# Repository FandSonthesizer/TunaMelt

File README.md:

# TunaMelt
Our Tuna Melt clone. 

This is out attempt to build a Tuna Melt clone. We changed it to have a true bypass, also we are using standart parts which are not hard to get by.
The Vactrol consists of an LDR03 light sensitive resistor and a white 3mm LED, bound together head on head with some black electrical tape.

So we re-named it the FnS Melt. :-)

This effect just sounds great, a very nice Tremolo indeed!

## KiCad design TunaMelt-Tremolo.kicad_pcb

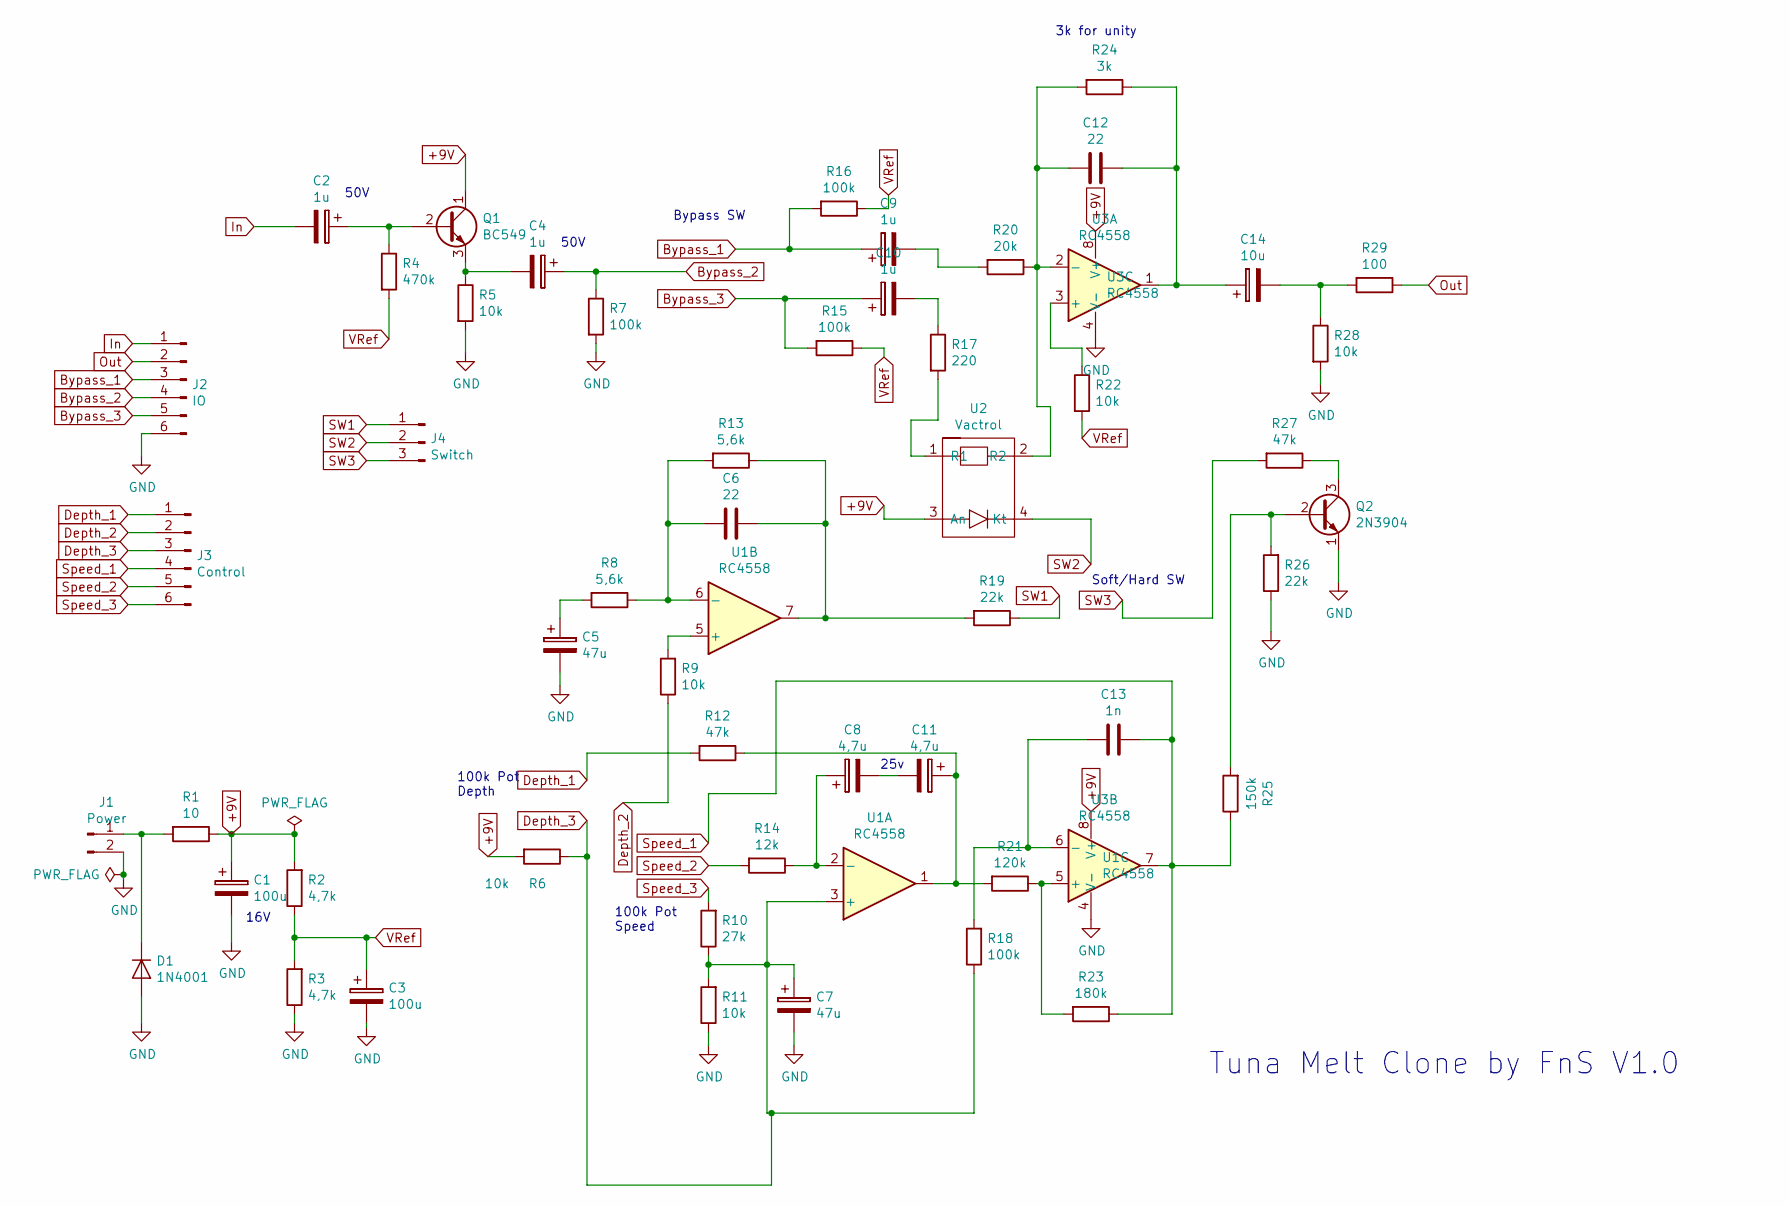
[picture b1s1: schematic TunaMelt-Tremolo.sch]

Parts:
C1, C3: 100u; Elko_D6.3mm_P2.50mm
C2, C4, C9, C10: 1u; Elko_D6.3mm_P2.50mm
C5, C7: 47u; Elko_D6.3mm_P2.50mm
C6, C12: 22; Kondensator_Keramik
C8, C11: 4,7u; Elko_D6.3mm_P2.50mm
C13: 1n; Kondensator_Keramik
C14: 10u; Elko_D6.3mm_P2.50mm
D1: 1N4001; Diode_Horizontal
J1: Power; Stift_x02
J2: IO; PinHeader_1x06_P2.54mm_Vertical_NIK
J3: Control; PinHeader_1x06_P2.54mm_Vertical_NIK
J4: Switch; Stift_0x3
Q1: BC549; TO-92_Wide_NIK
Q2: 2N3904; TO-92_Wide_NIK
R1: 10; Widerstand_liegend
R2, R3: 4,7k; Widerstand_liegend
R4: 470k; Widerstand_liegend
R5, R6, R9, R11, R22, R28: 10k; Widerstand_liegend
R7, R15, R16, R18: 100k; Widerstand_liegend
R8, R13: 5,6k; Widerstand_liegend
R10: 27k; Widerstand_liegend
R12, R27: 47k; Widerstand_liegend
R14: 12k; Widerstand_liegend
R17: 220; Widerstand_liegend
R19, R26: 22k; Widerstand_liegend
R20: 20k; Widerstand_liegend
R21: 120k; Widerstand_liegend
R23: 180k; Widerstand_liegend
R24: 3k; Widerstand_liegend
R25: 150k; Widerstand_liegend
R29: 100; Widerstand_liegend
U1, U3: RC4558; DIP-8_W7.62mm_Socket_LongPads
U2: Vactrol

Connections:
+9V: C1.1, Q1.1 (C), R1.1, R2.2, R6.2, U1.8 (V+), U2.3 (An), U3.8 (V+)
Bypass_1: C9.1, J2.3, R16.2
Bypass_2: C4.1, J2.4, R7.1
Bypass_3: C10.1, J2.5, R15.2
Depth_1: J3.1, R12.2
Depth_2: J3.2, R9.1
Depth_3: C7.1, J3.3, R6.1, R10.1, R11.2, R18.1, U1.3 (+)
GND: C1.2, C3.2, C5.2, C7.2, D1.2 (A), J1.2, J2.6, Q2.1 (E), R3.1, R5.2, R7.2, R11.1, R26.1, R28.2, U1.4 (V-), U3.4 (V-)
In: C2.2, J2.1
unnamed: C2.1, Q1.2 (B), R4.1
unnamed: C4.2, Q1.3 (E), R5.1
unnamed: C5.1, R8.2
unnamed: C6.1, R13.1, R19.2, U1.7
unnamed: C6.2, R8.1, R13.2, U1.6 (-)
unnamed: C8.1, R14.1, U1.2 (-)
unnamed: C9.2, R20.2
unnamed: C10.2, R17.1
unnamed: C11.1, R12.1, R21.2, U1.1
unnamed: C8.2, C11.2
unnamed: C12.1, C14.1, R24.1, U3.1
unnamed: C12.2, R20.1, R24.2, U2.2 (R2), U3.2 (-)
unnamed: C13.2, R18.2, U3.6 (-)
unnamed: C14.2, R28.1, R29.2
unnamed: D1.1 (K), J1.1, R1.2
unnamed: Q2.2 (B), R25.2, R26.2
unnamed: Q2.3 (C), R27.1
unnamed: R9.2, U1.5 (+)
unnamed: R17.2, U2.1 (R1)
unnamed: R21.1, R23.2, U3.5 (+)
unnamed: R22.1, U3.3 (+)
Out: J2.2, R29.1
SW1: J4.1, R19.1
SW2: J4.2, U2.4 (Kt)
SW3: J4.3, R27.2
Speed_1: C13.1, J3.4, R23.1, R25.1, U3.7
Speed_2: J3.5, R14.2
Speed_3: J3.6, R10.2
VRef: C3.1, R2.1, R3.2, R4.2, R15.1, R16.1, R22.2

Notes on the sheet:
50V
Bypass SW
Soft/Hard SW
100k Pot Depth
100k Pot Speed
16V
25v
Tuna Melt Clone by FnS V1.0
3k for unity

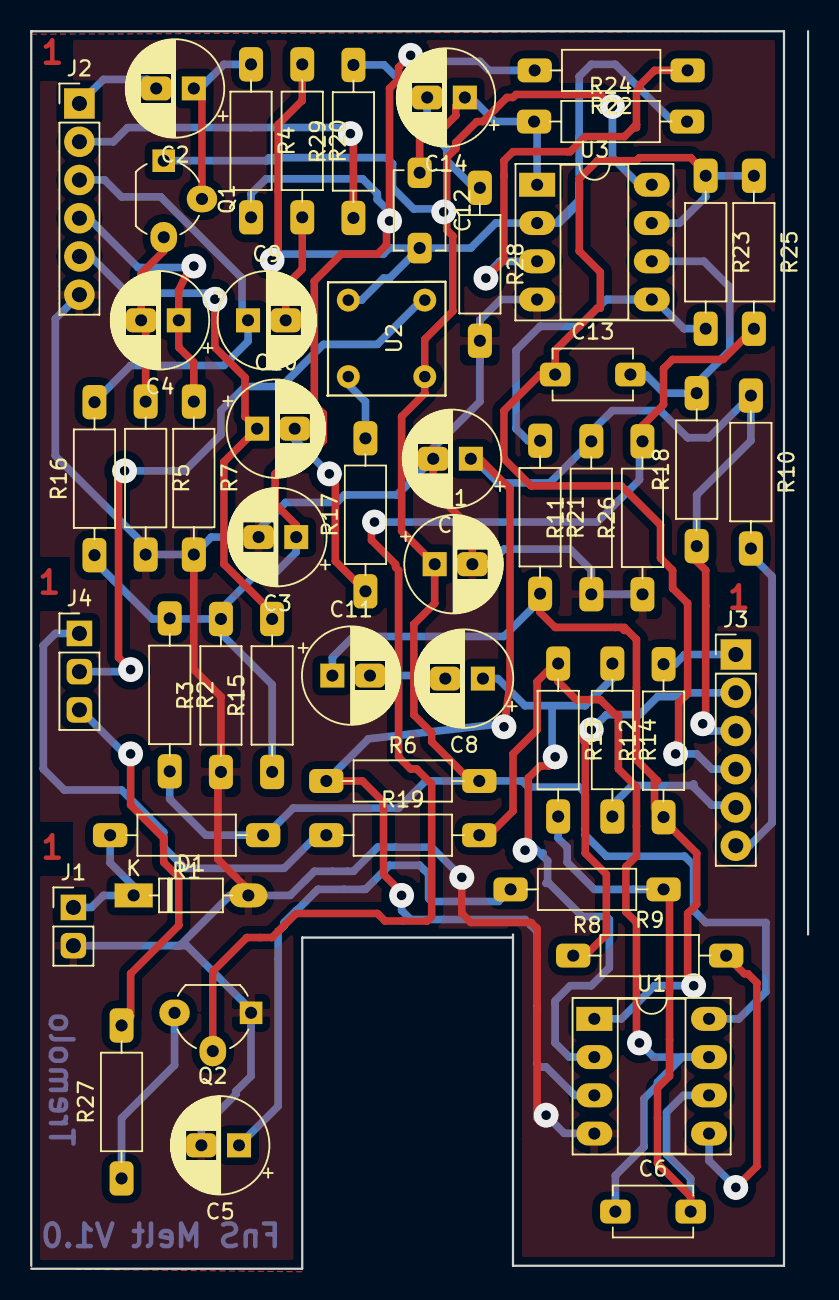
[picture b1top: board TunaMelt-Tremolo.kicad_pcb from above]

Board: 2 copper layers, 51.6 x 82.2 mm, 53 parts (0 on the bottom side), 38 nets.
